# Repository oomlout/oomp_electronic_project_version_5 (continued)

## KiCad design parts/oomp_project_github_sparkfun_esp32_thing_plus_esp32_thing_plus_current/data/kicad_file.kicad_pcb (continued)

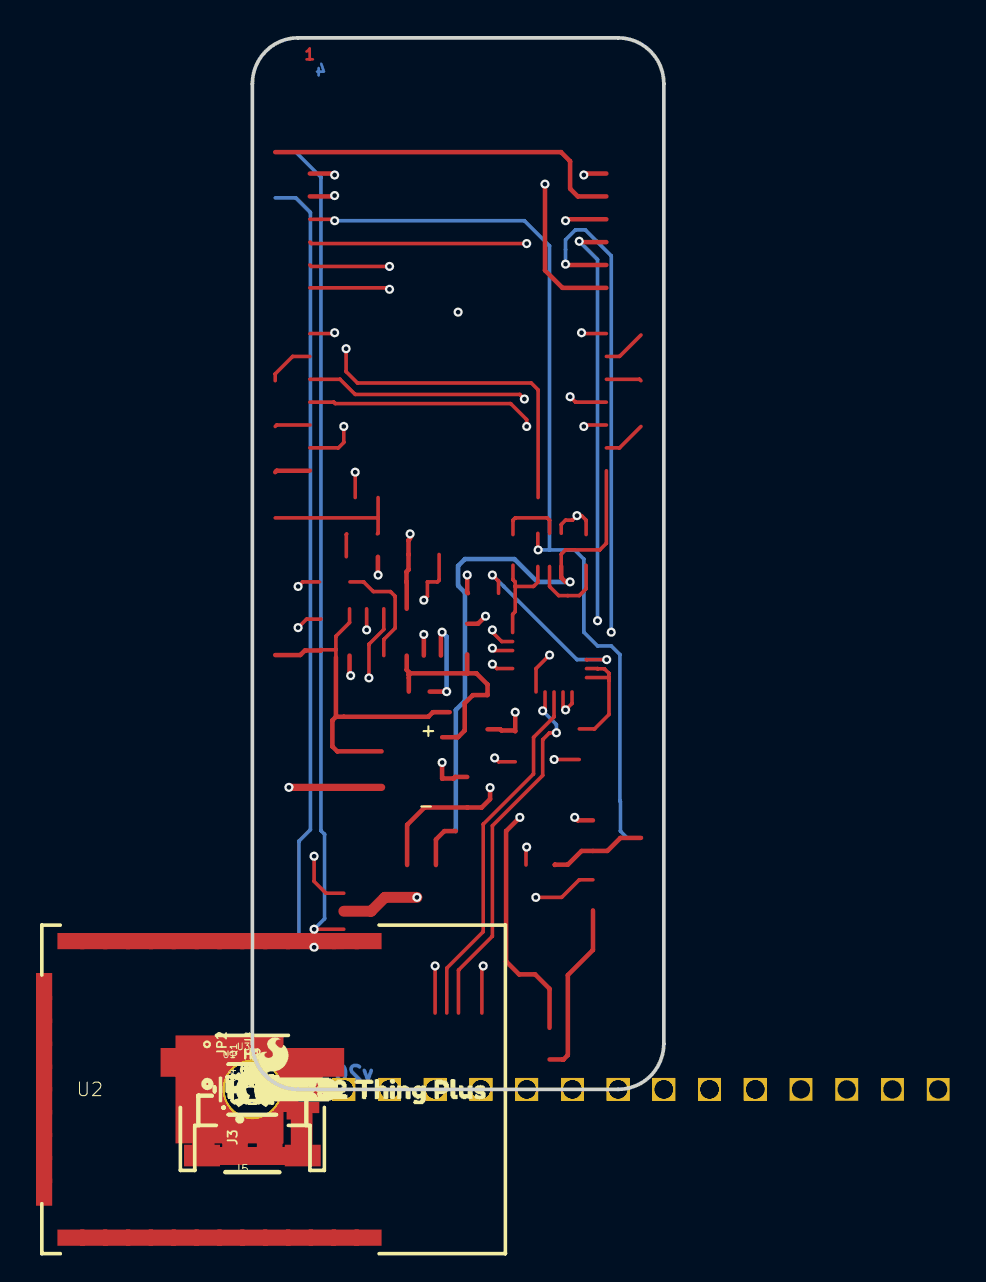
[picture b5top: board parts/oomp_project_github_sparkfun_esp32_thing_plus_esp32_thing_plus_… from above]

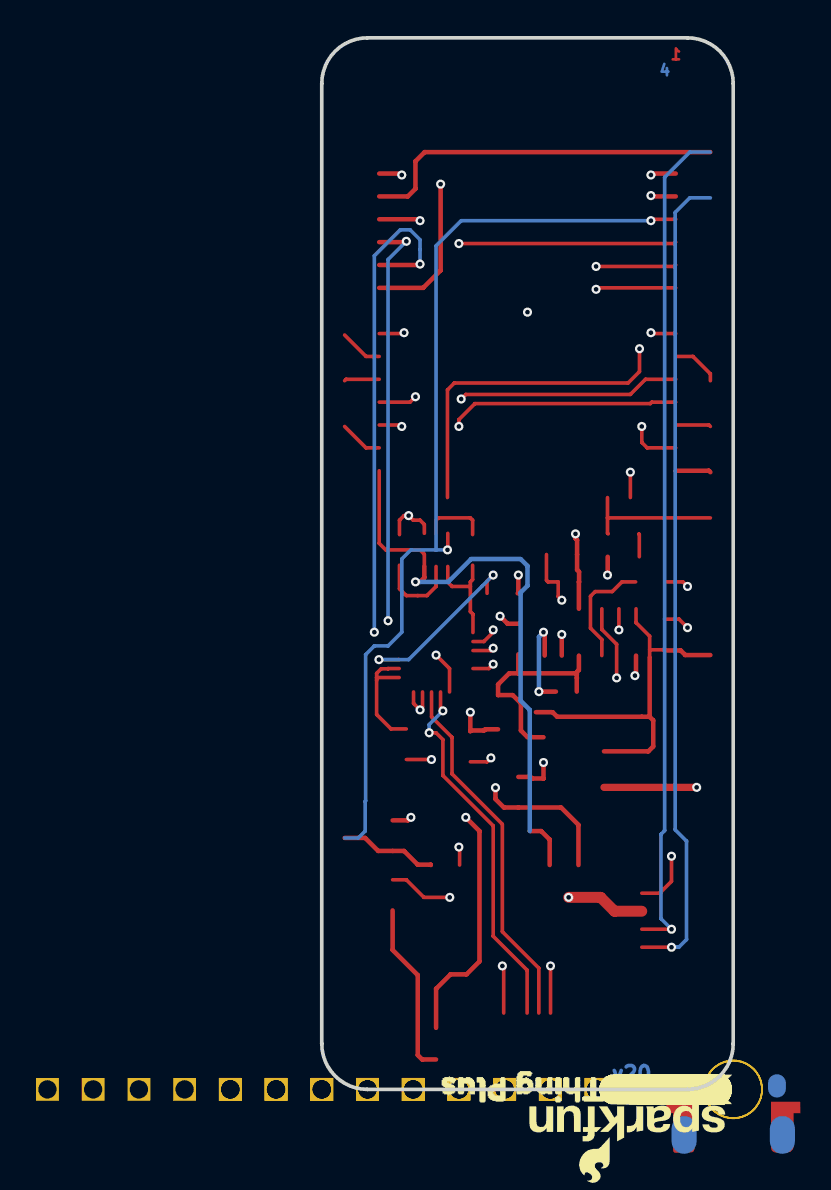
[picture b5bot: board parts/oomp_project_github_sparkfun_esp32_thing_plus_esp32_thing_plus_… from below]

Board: 4 copper layers, 22.9 x 58.4 mm, 107 parts (32 on the bottom side), 43 nets.

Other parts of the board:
U$1: #RESET0
U$2: 3V31
U$3: 1323
U$4: 1417
U$5: 1519
U$6: 16#RX11
U$7: 17#TX10
U$8: 121
U$9: 210
U$10: 2721
U$11: 3218
U$12: 3320
U$13: A03
U$14: A14
U$15: A25
U$16: A36
U$17: A47
U$18: A58
U$19: EN26
U$20: GND2
U$21: 22#SCL1
U$22: 23#SDA0
U$23: QWIIC27
U$27: VBAT25
U$28: VUSB24
U$29: SDA1
U$30: SCL0
U$31: 142
U$32: 323
U$33: 154
U$34: 335
U$35: 276
U$36: 127
U$37: 138
U$38: 219
U$39: 1710
U$40: 1611
U$41: A515
U$42: A416
U$43: A317
U$44: A218
U$45: A119
U$46: A020
U$47: SCK20
U$48: GND21
U$49: NC22
U$50: VUSB8
U$51: EN9
U$52: VBAT10
U$53: 137
U$54: MISO0
U$55: MOSI1
U$56: CHG1
U$57: RESET0
U$58, U$65: ESP32_THING_PLUS0
U$59: ORDERING_INSTRUCTIONS
U$60: 3V323
U$61: RST24
U$62: 00
U$63: 5#SCK2
U$64: NC0
U$66: 18#MOSI1
U$67: 19#MISO0

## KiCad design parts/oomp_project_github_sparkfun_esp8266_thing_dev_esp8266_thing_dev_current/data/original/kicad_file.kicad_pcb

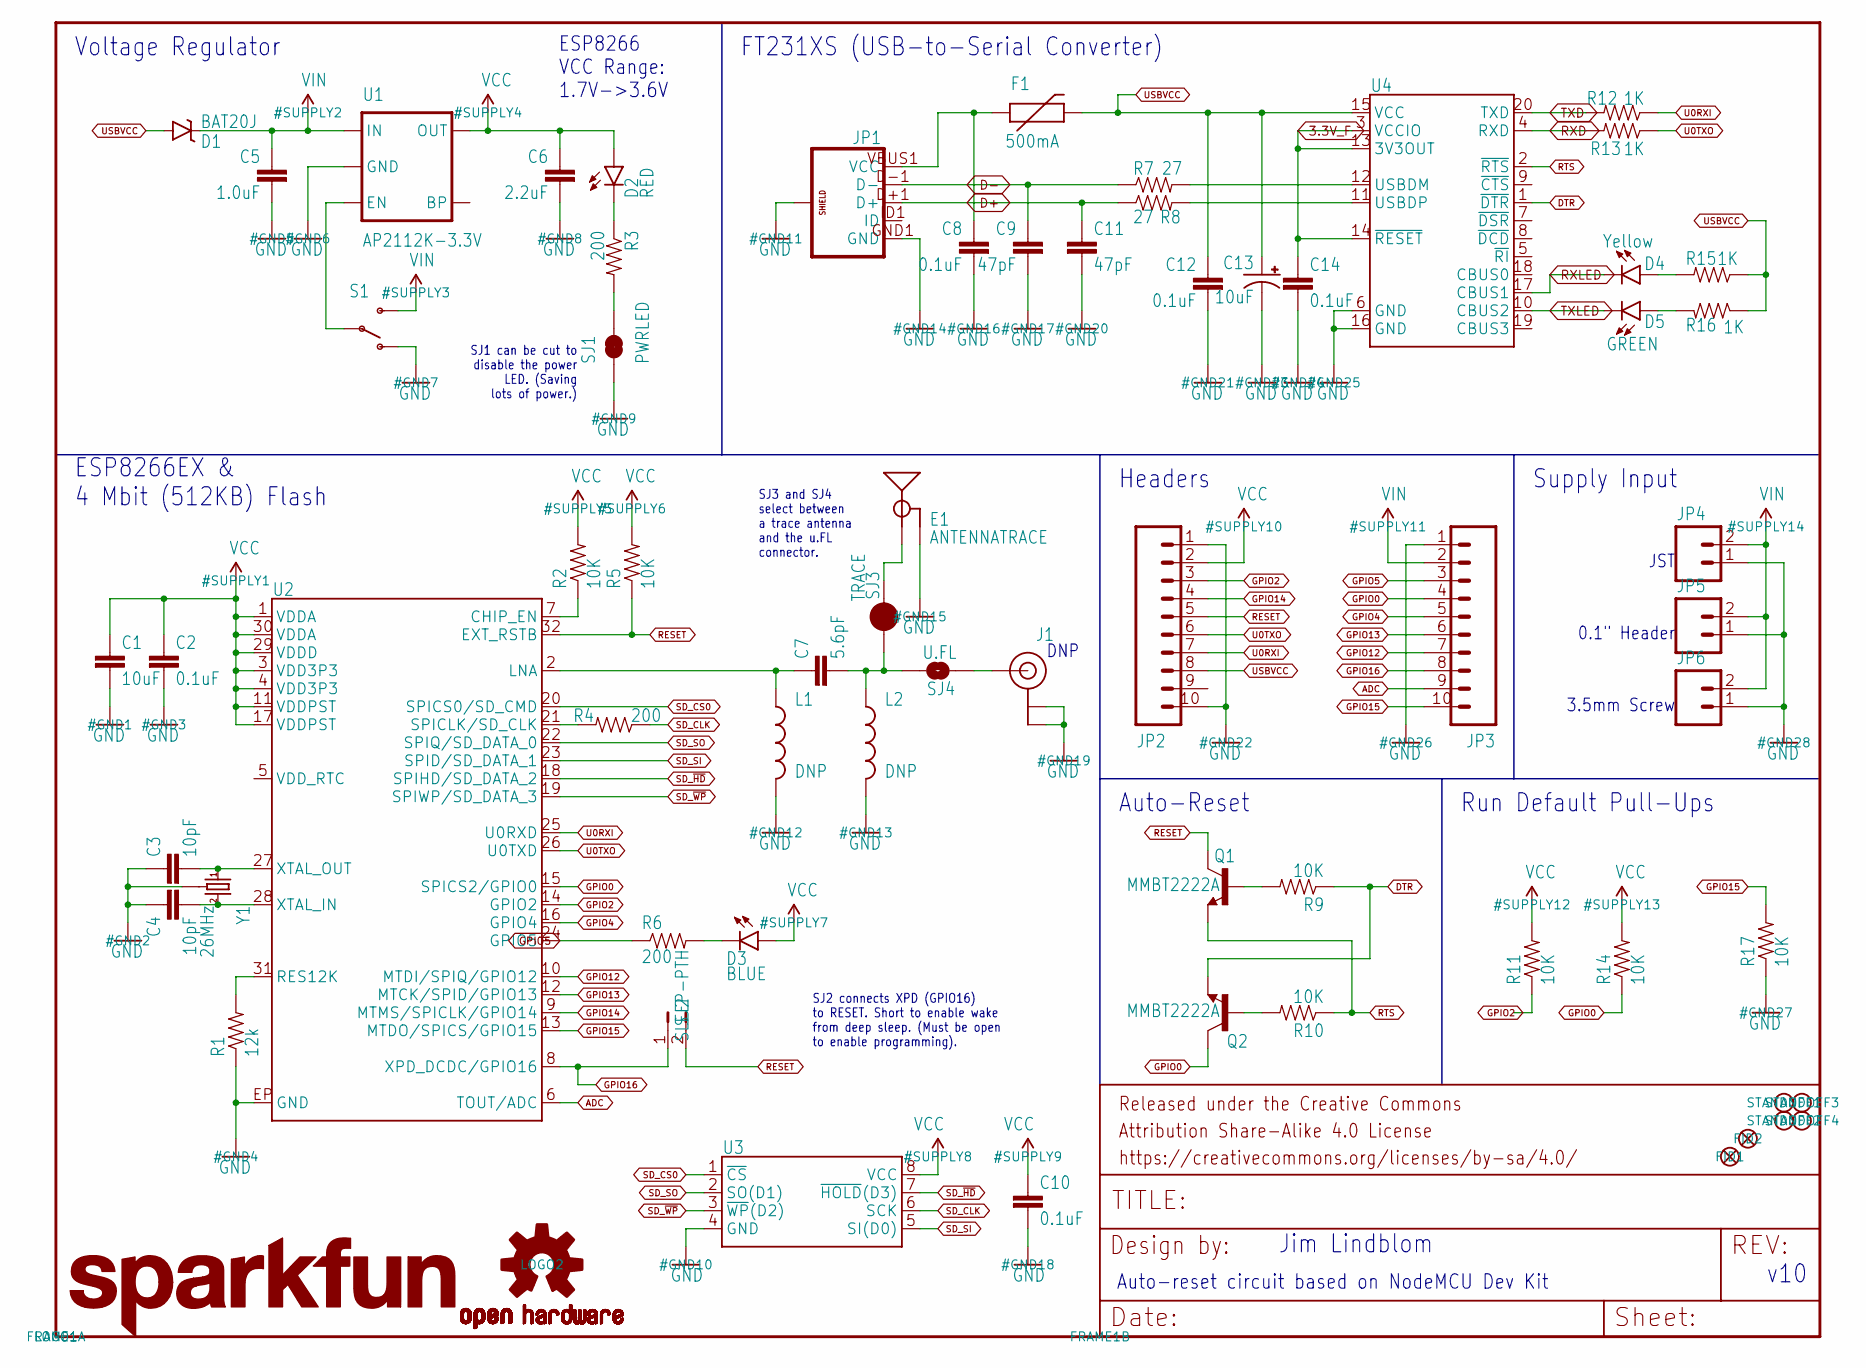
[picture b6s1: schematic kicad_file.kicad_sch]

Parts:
C1: 10uF; 0603-CAP
C2, C8, C10, C12, C14: 0.1uF; 0603-CAP
C3, C4: 10pF; 0603-CAP
C5: 1.0uF; 0805
C6: 2.2uF; 0603-CAP
C7: 5.6pF; 0603-CAP
C9, C11: 47pF; 0603-CAP
C13: 10uF; EIA3216
D1: BAT20J; SOD-323
D2: RED; LED-0603
D3: BLUE; LED-0603
D4: Yellow; LED-0603
D5: GREEN; LED-0603
E1: ANTENNATRACE; TRACE_ANTENNA_2.4GHZ_25.7MM
F1: 500mA; PTC-1206
FID1, FID2: FIDUCIAL1X2; FIDUCIAL-1X2
FRAME1: FRAME-LETTER; CREATIVE_COMMONS
J1: DNP; U.FL
JP1: USB_MICROB_PLUGCONN-11752; USB-B-MICRO-SMD_V03
JP2, JP3: M10NO_SILK_PTH_FEMALE; 1X10_NO_SILK
JP4: M02JST-PTH-2; JST-2-PTH
JP5: M021X02_NO_SILK; 1X02_NO_SILK
JP6: M023.5MM-NO_SILK; SCREWTERMINAL-3.5MM-2-NS
L1, L2: DNP; 0603
LOGO1: SFE_LOGO_NAME.2_INCH; SFE_LOGO_NAME_.2
LOGO2: OSHW-LOGOS; OSHW-LOGO-S
Q1, Q2: MMBT2222A; SOT23-3
R1: 12k; 0603-RES
R2, R5, R9, R10, R11, R14, R17: 10K; 0603-RES
R3, R4, R6: 200; 0603-RES
R7, R8: 27; 0603-RES
R12, R13, R15, R16: 1K; 0603-RES
S1: SWITCH-SPDT-SMD-A; SWITCH-SPST-SMD-A
SJ1: PWRLED; PAD-JUMPER-2-NC_BY_TRACE_YES_SILK
SJ2: SLEEP-PTH; PTH-JUMPER-2-NO_NO_SILK
SJ3: TRACE; PAD-JUMPER-2-NC_BY_PASTE_NO_SILK
SJ4: U.FL; PAD-JUMPER-2-NO_NO_SILK
STANDOFF1, STANDOFF2, STANDOFF3, STANDOFF4: STAND-OFF
U1: AP2112K-3.3V; SOT23-5
U2: ESP8266; QFN32
U3: AT25SF041-SOIC8; SO08
U4: FTS31XS-U; SSOP20_L
Y1: 26MHz; CRYSTAL-SMD-3.2X2.5

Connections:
3.3V_F: C14.1, U4.3 (VCCIO), U4.13 (3V3OUT), U4.14 (~RESET)
ADC: JP3.9, U2.6 (TOUT/ADC)
ANT: J1.P$3 (SIGNAL), SJ4.1
CHIP_EN: R2.1, U2.7 (CHIP_EN)
D+: C11.1, JP1.D+1 (D+), R8.1
D-: C9.1, JP1.D-1 (D-), R7.1
DTR: Q2.2 (E), R9.1, U4.1 (~DTR)
GND: C1.2, C2.2, C3.1, C4.1, C5.2, C6.2, C8.2, C9.2, C10.2, C11.2, C12.2, C13.C (-), C14.2, E1.GND, E1.GND2 (GND), J1.P$1 (GND), J1.P$2 (GND), JP1.GND1 (GND), JP1.SHIELD1 (SHIELD), JP1.SHIELD2 (SHIELD), JP1.SHIELD3 (SHIELD), JP2.1, JP2.10, JP3.1, JP4.1, JP5.1, JP6.1, L1.2, L2.2, R1.1, R17.1, S1.1 (O), SJ1.1, U1.2 (GND), U2.EP (GND), U3.4 (GND), U4.6 (GND), U4.16 (GND), Y1.2 (GND), Y1.4 (GND)
GPIO0: JP3.4, Q2.3 (C), R14.1, U2.15 (SPICS2/GPIO0)
GPIO2: JP2.3, R11.1, U2.14 (GPIO2)
GPIO4: JP3.5, U2.16 (GPIO4)
GPIO5: JP3.3, R6.1, U2.24 (GPIO5)
GPIO12: JP3.7, U2.10 (MTDI/SPIQ/GPIO12)
GPIO13: JP3.6, U2.12 (MTCK/SPID/GPIO13)
GPIO14: JP2.4, U2.9 (MTMS/SPICLK/GPIO14)
GPIO15: JP3.10, R17.2, U2.13 (MTDO/SPICS/GPIO15)
GPIO16: JP3.8, SJ2.1, U2.8 (XPD_DCDC/GPIO16)
LNA: C7.1, L1.1, U2.2 (LNA)
LNA2: C7.2, L2.1, SJ3.1, SJ4.2
unnamed: R1.2, U2.31 (RES12K)
unnamed: C4.2, U2.28 (XTAL_IN), Y1.3 (2)
unnamed: C3.2, U2.27 (XTAL_OUT), Y1.1
unnamed: R7.2, U4.12 (USBDM)
unnamed: R3.2, SJ1.2
unnamed: Q1.1 (B), R9.2
unnamed: R8.2, U4.11 (USBDP)
unnamed: D5.A, R16.2
unnamed: D3.C, R6.2
unnamed: D4.A, R15.2
unnamed: D2.C, R3.1
unnamed: Q2.1 (B), R10.2
unnamed: S1.2, U1.3 (EN)
RESET: JP2.5, Q1.3 (C), R5.1, SJ2.2, U2.32 (EXT_RSTB)
RTS: Q1.2 (E), R10.1, U4.2 (~RTS)
RXD: R13.2, U4.4 (RXD)
RXLED: D4.C, U4.17 (CBUS1)
SD_CLK: R4.1, U3.6 (SCK)
SD_CLK0: R4.2, U2.21 (SPICLK/SD_CLK)
SD_CS0: U2.20 (SPICS0/SD_CMD), U3.1 (~CS)
SD_SI: U2.23 (SPID/SD_DATA_1), U3.5 (SI(D0))
SD_SO: U2.22 (SPIQ/SD_DATA_0), U3.2 (SO(D1))
SD_~HD: U2.18 (SPIHD/SD_DATA_2), U3.7 (~HOLD(D3))
SD_~WP: U2.19 (SPIWP/SD_DATA_3), U3.3 (~WP(D2))
TRACE_ANT: E1.ANT (SIGNAL), SJ3.2
TXD: R12.2, U4.20 (TXD)
TXLED: D5.C, U4.10 (CBUS2)
U0RXI: JP2.7, R12.1, U2.25 (U0RXD)
U0TXO: JP2.6, R13.1, U2.26 (U0TXD)
USBVCC: C12.1, C13.A (+), D1.A, F1.2, JP2.8, R15.1, R16.1, U4.15 (VCC)
VCC: C1.1, C2.1, C6.1, C10.1, D2.A, D3.A, JP2.2, R2.2, R5.2, R11.2, R14.2, U1.5 (OUT), U2.1 (VDDA), U2.3 (VDD3P3), U2.4 (VDD3P3), U2.11 (VDDPST), U2.17 (VDDPST), U2.29 (VDDD), U2.30 (VDDA), U3.8 (VCC)
VIN: C5.1, D1.C, JP3.2, JP4.2, JP5.2, JP6.2, S1.3 (S), U1.1 (IN)
VUSB: C8.1, F1.1, JP1.VBUS1 (VCC)

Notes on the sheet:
DNP
Jim Lindblom
Supply Input
ESP8266 VCC Range: 1.7V->3.6V
3.5mm Screw
Auto-reset circuit based on NodeMCU Dev Kit
0.1" Header
Auto-Reset
ESP8266EX & 4 Mbit (512KB) Flash
SJ2 connects XPD (GPIO16) to RESET. Short to enable wake from deep sleep. (Must be open to enable programming).
JST
Voltage Regulator
SJ1 can be cut to disable the power LED. (Saving lots of power.)
SJ3 and SJ4 select between a trace antenna and the u.FL connector.
Headers
Run Default Pull-Ups
v10
FT231XS (USB-to-Serial Converter)

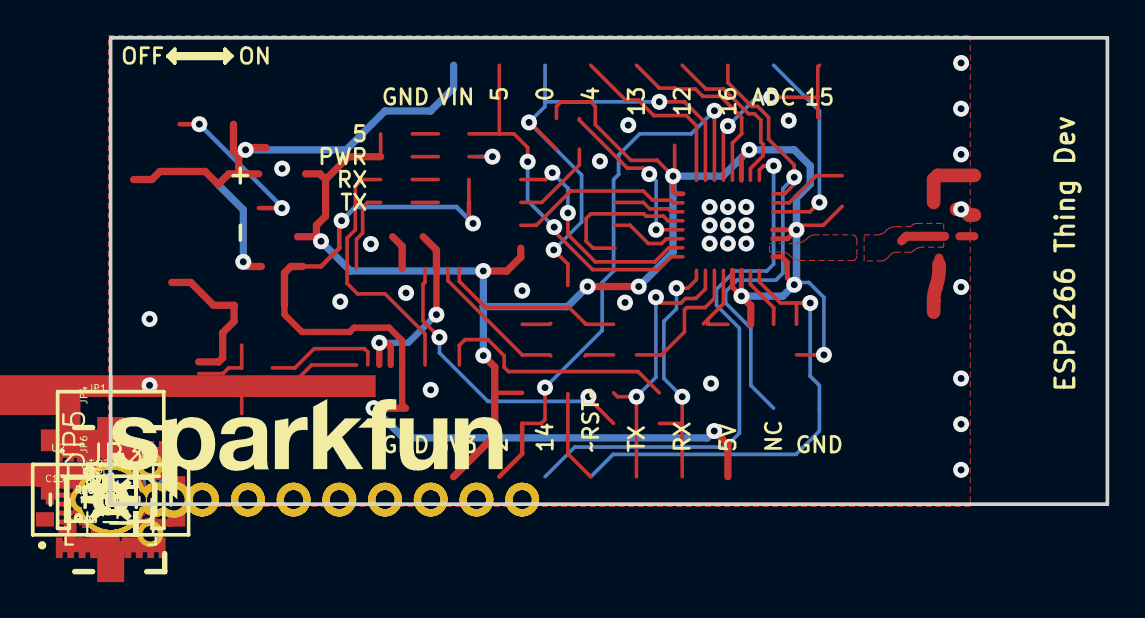
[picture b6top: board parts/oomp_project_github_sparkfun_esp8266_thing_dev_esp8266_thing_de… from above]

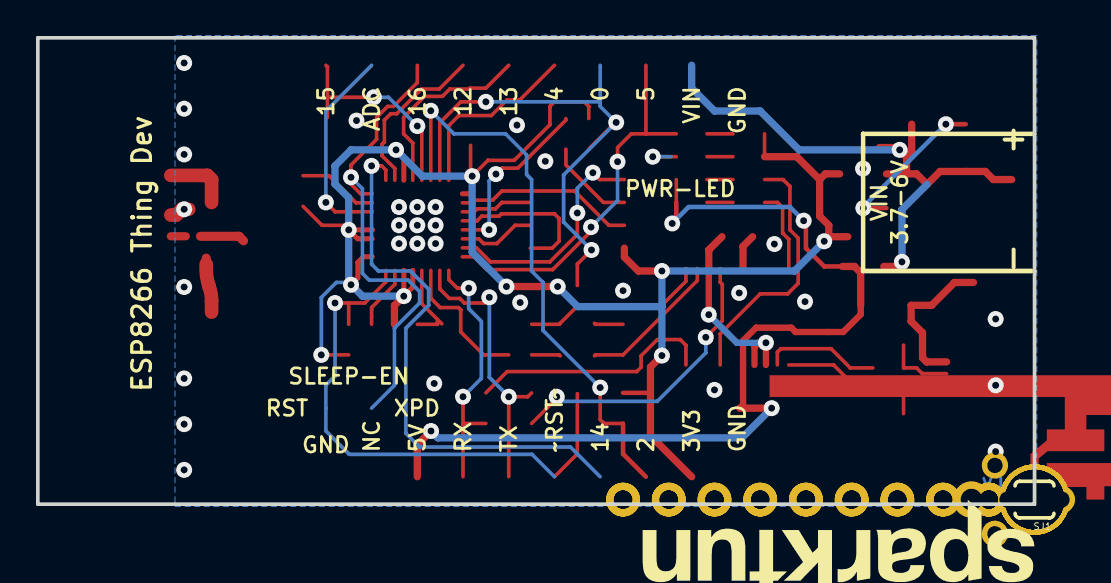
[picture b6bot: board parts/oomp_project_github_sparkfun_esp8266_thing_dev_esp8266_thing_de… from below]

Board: 2 copper layers, 55.4 x 25.9 mm, 69 parts (2 on the bottom side), 52 nets.

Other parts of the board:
LOGO3: SFE_LOGO_NAME.2_INCH; SFE_LOGO_NAME_.2

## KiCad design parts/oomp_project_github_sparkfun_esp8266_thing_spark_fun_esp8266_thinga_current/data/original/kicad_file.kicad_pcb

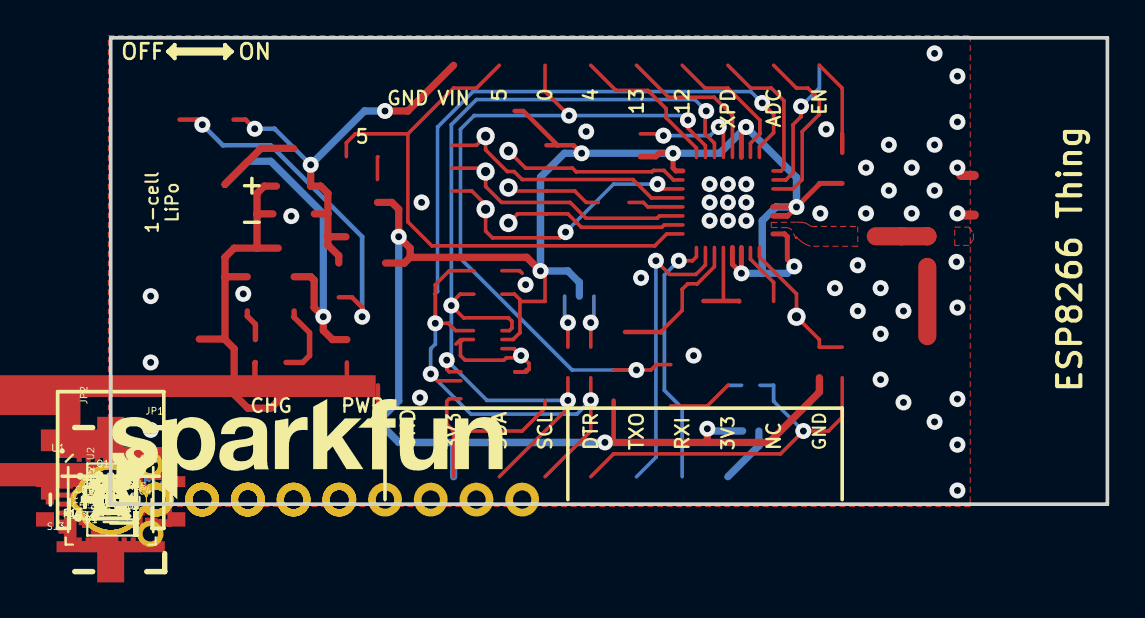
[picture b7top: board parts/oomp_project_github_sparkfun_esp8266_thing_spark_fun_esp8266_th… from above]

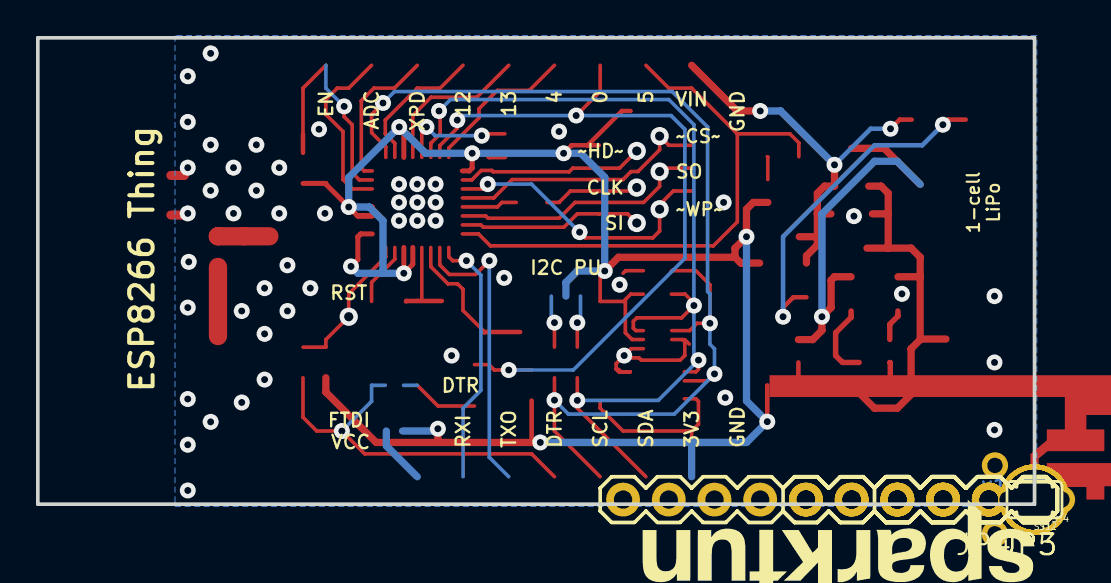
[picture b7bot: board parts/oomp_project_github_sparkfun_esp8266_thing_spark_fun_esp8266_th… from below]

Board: 2 copper layers, 55.4 x 25.9 mm, 73 parts (14 on the bottom side), 44 nets.

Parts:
C1: 10uF; 0603-CAP
C2, C10: 0.1uF; 0603-CAP
C3, C4: 10pF; 0603-CAP
C5: 4.7uF; 0603-CAP
C6: 1.0uF; 0603-CAP
C7: 1.0uF; 0805
C8: 5.6pF; 0603-CAP
C9: 2.2uF; 0603-CAP
C11, C12: DNP; 0603-CAP
D1: YELLOW; LED-0603
D2: GREEN; LED-0603
D3: BAT20J; SOD-323
D4: RED; LED-0603
D5: SOD-323
E1: ANTENNATRACE; TRACE_ANTENNA_2.4GHZ_25.7MM
FID1, FID2: FIDUCIAL1X2; FIDUCIAL-1X2
FRAME1: FRAME-LETTER; CREATIVE_COMMONS
J1: DNP; U.FL
JP1: USB; USB-B-MICRO-SMD_V03
JP2: LiPo; JST-2-PTH
JP3: M10"; 1X10
JP4: FTDI_BASICPTH; FTDI_BASIC
JP5: I2C; 1X04
L1, L2: DNP; 0603
LOGO1, LOGO5: SFE_LOGO_NAME.2_INCH; SFE_LOGO_NAME_.2
LOGO3: SFE_LOGO_FLAME.1_INCH; SFE_LOGO_FLAME_.1
LOGO4: OSHW-LOGOS; OSHW-LOGO-S
Q1: 2.5A/30V; SOT23-3
R1: 12k; 0603-RES
R2, R5, R8, R16: 200; 0603-RES
R3, R6, R7, R17: 10K; 0603-RES
R4: 2.0k; 0603-RES
R9: 0; 0603
R10: DNP; 0603-RES
R11, R13: 2.2k; 0603-RES
R15: 1K; 0603-RES
S1: SWITCH-SPST-SMD-A
SJ1: PAD-JUMPER-2-NC_BY_TRACE_YES_SILK
SJ2: PAD-JUMPER-3-3OF3_NC_BY_TRACE_YES_SILK_FULL_BOX
SJ3: PTH-JUMPER-NC_BOTTOM_NO_SILK
SJ4: PAD-JUMPER-2-NO_YES_SILK
STANDOFF1, STANDOFF2, STANDOFF3, STANDOFF4: STAND-OFF
TP1, TP2, TP3, TP4, TP5, TP6, TP7: PAD.03X.05
U1: ESP8266; QFN32
U2: MCP73831; SOT23-5
U3: AT25SF041-SOIC8; SO08
U4: AP2112K-3.3V; SOT23-5
U5: DNP; UDFN8
U6: DNP; SOT563-2
U7: DNP; FN-6
Y1: 26MHz; CRYSTAL-SMD-3.2X2.5

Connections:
ADC: JP3.9, U1.6
ANT: J1.P$3, R10.1
CHIP_EN: JP3.10, R3.1, U1.7
DTR: C6.2, JP4.DTR, SJ1.2, SJ3.1
FTDI_VCC: JP4.VCC, SJ4.1
GND: C1.2, C2.2, C3.1, C4.1, C5.2, C7.2, C9.2, C10.2, C11.2, C12.2, E1.GND, E1.GND2, J1.P$1, J1.P$2, JP1.GND1, JP1.SHIELD1, JP1.SHIELD2, JP1.SHIELD3, JP2.1, JP3.1, JP4.GND, JP5.1, L1.2, L2.2, R1.1, R4.1, R7.1, R8.2, R16.2, R17.1, S1.1, U1.EP, U2.2, U3.4, U4.2, U5.4, U6.2, U6.4, U7.2, U7.3, Y1.2, Y1.4
GPIO0: D5.A, JP3.4, R15.1, U1.15
GPIO2/SDA: JP5.3, R11.1, U1.14, U5.5, U6.6, U7.6
GPIO4: JP3.5, U1.16
GPIO5: D2.A, JP3.3, U1.24
GPIO12: JP3.7, U1.10
GPIO13: JP3.6, U1.12
GPIO14/SCL: JP5.4, R13.1, U1.9, U5.6, U6.1, U7.4
GPIO15: R17.2, U1.13
GPIO16: JP3.8, U1.8
LNA: C8.1, L1.1, U1.2
unnamed: R1.2, U1.31
unnamed: C4.2, U1.28, Y1.3
unnamed: C3.2, U1.27, Y1.1
unnamed: D4.C, R16.1
unnamed: C8.2, L2.1, R9.2, R10.2
unnamed: R5.2, U1.21
unnamed: D5.C, SJ1.1, SJ3.2
unnamed: R11.2, SJ2.1
unnamed: R13.2, SJ2.3
unnamed: S1.2, U4.3
unnamed: R4.2, U2.5
unnamed: D2.C, R8.1
unnamed: D1.C, R2.2
unnamed: R2.1, U2.1
RESET: C6.1, R6.1, TP7.P$1, U1.32
SD_CLK: R5.1, TP3.P$1, U3.6
SD_CS0: TP6.P$1, U1.20, U3.1
SD_SI: TP2.P$1, U1.23, U3.5
SD_SO: TP5.P$1, U1.22, U3.2
SD_~HD: TP4.P$1, U1.18, U3.7
SD_~WP: TP1.P$1, U1.19, U3.3
TRACE_ANT: E1.ANT, R9.1
U0RXI: JP4.TXO, U1.25
U0TXO: JP4.RXI, U1.26
VBAT: C5.1, JP2.2, Q1.3, U2.3
VCC: C1.1, C2.1, C9.1, C10.1, C11.1, C12.1, D4.A, JP5.2, R3.2, R6.2, R15.2, SJ2.2, SJ4.2, U1.1, U1.3, U1.4, U1.11, U1.17, U1.29, U1.30, U3.8, U4.5, U5.8, U6.5, U7.1
VIN: C7.1, D3.C, JP3.2, Q1.2, S1.3, U4.1
VUSB: D1.A, D3.A, JP1.VBUS1, Q1.1, R7.2, U2.4

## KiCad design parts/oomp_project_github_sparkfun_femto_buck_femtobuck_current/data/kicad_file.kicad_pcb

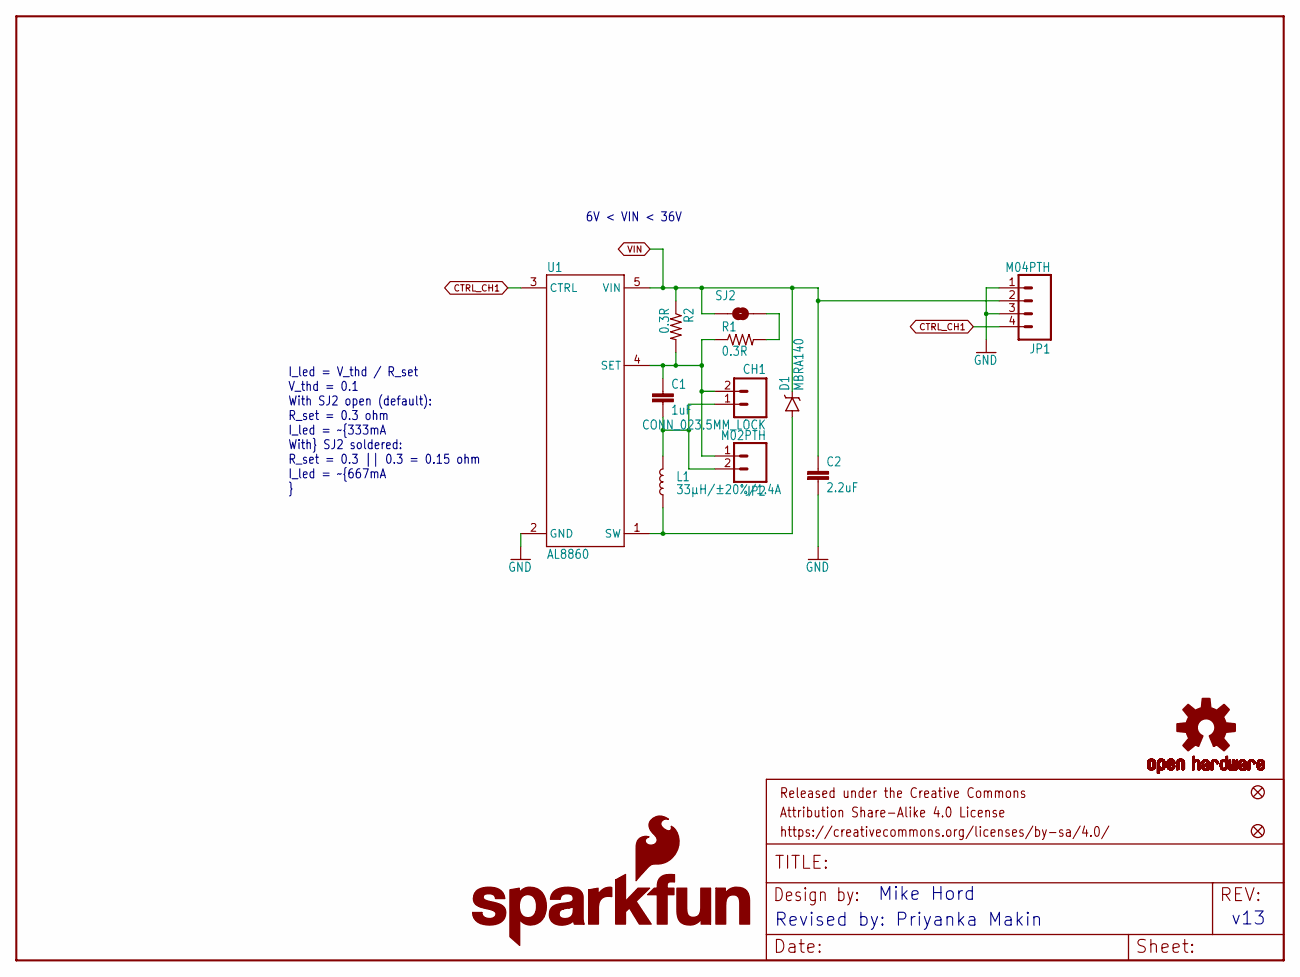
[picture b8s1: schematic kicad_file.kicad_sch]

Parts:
C1: 1uF; 1206-CAP
C2: 2.2uF; 1206-CAP
CH1: CONN_023.5MM_LOCK; SCREWTERMINAL-3.5MM-2_LOCK
D1: MBRA140; SMA-DIODE
FID1, FID2: FIDUCIAL1X2; FIDUCIAL-1X2
FRAME1: FRAME-LETTER; CREATIVE_COMMONS
JP1: M04PTH; 1X04
JP2: M02PTH; 1X02@1
L1: 33µH/±20%/1.4A; SRN6045
LOGO1: OSHW-LOGOS; OSHW-LOGO-S
LOGO2: SFE_LOGO_NAME_FLAME.1_INCH; SFE_LOGO_NAME_FLAME_.1
R1, R2: 0.3R; 0805
SJ2: NO Jumper; SMT-JUMPER_2_NO_NO-SILK
U1: AL8860; SOT23-5

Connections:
CTRL_CH1: JP1.4, U1.3 (CTRL)
GND: C2.2, JP1.1, JP1.3, U1.2 (GND)
unnamed: R1.2, SJ2.2
OUT+: C1.1, CH1.2, JP2.1, R1.1, R2.2, U1.4 (SET)
OUT-: C1.2, CH1.1, JP2.2, L1.2
SW: D1.A, L1.1, U1.1 (SW)
VIN: C2.1, D1.C, JP1.2, R2.1, SJ2.1, U1.5 (VIN)

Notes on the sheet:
6V < VIN < 36V
Mike Hord
Revised by: Priyanka Makin
v13
I_led = V_thd / R_set V_thd = 0.1 With SJ2 open (default): R_set = 0.3 ohm I_led = ~{333mA With} SJ2 soldered: R_set = 0.3 || 0.3 = 0.15 ohm I_led = ~{667mA }

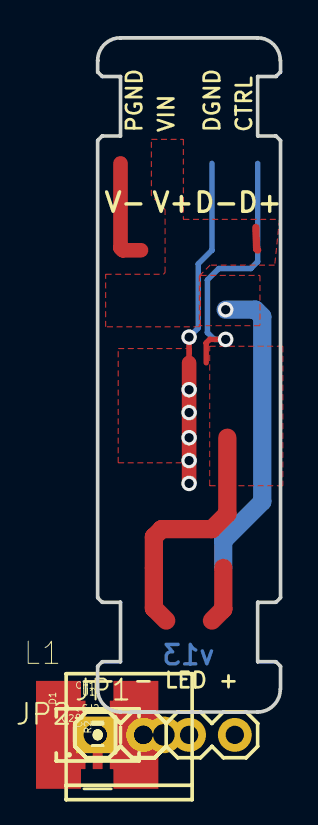
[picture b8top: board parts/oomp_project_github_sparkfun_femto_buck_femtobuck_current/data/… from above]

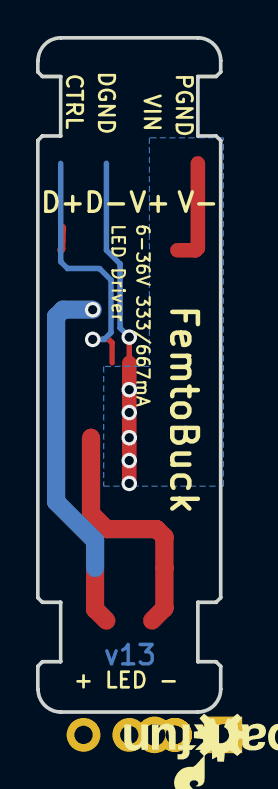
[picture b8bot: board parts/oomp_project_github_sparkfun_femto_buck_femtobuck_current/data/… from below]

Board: 4 copper layers, 10.2 x 37.5 mm, 16 parts (2 on the bottom side), 7 nets.

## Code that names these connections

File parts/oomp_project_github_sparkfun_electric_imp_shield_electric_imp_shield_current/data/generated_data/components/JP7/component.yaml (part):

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      position:
        x: 254.0
        y: 147.32
      net: PIN9
      net_aliases:
      - PIN9
      net_scope: global
      no_connect: false
      connected_to:
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      position:
        x: 254.0
        y: 144.78
      net: PIN8
      net_aliases:
      - PIN8
      net_scope: global
      no_connect: false
      connected_to:
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      position:
        x: 254.0
        y: 142.24
      net: PIN7
      net_aliases:
      - PIN7
      net_scope: global
      no_connect: false
      connected_to:
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      position:
        x: 254.0
        y: 139.7
      net: PIN5
      net_aliases:
      - PIN5
      net_scope: global
      no_connect: false
      connected_to:
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      position:
        x: 254.0
        y: 137.16
      net: PIN2
      net_aliases:
      - PIN2
      net_scope: global
      no_connect: false
      connected_to:
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      position:
        x: 254.0
        y: 134.62
      net: PIN1
      net_aliases:
      - PIN1
      net_scope: global
      no_connect: false
      connected_to:
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    layers:
    - '*.Cu'
    - '*.Mask'
    net: PIN9
    net_number: null
    pin_function: null
    pin_type: null
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    layers:
    - '*.Cu'
    - '*.Mask'
    net: PIN8
    net_number: null
    pin_function: null
    pin_type: null
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    layers:
    - '*.Cu'
    - '*.Mask'
    net: PIN7
    net_number: null
    pin_function: null
    pin_type: null
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    layers:
    - '*.Cu'
    - '*.Mask'
    net: PIN5
    net_number: null
    pin_function: null
    pin_type: null
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    layers:
    - '*.Cu'
    - '*.Mask'
    net: PIN2
    net_number: null
    pin_function: null
    pin_type: null
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    layers:
    - '*.Cu'
    - '*.Mask'
    net: PIN1
    net_number: null
    pin_function: null
    pin_type: null
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    status: agree
  - pin_or_pad_number: '4'
    schematic_nets:
    - PIN9
    pcb_nets:
    - PIN9
    status: agree
  - pin_or_pad_number: '5'
    schematic_nets:
    - PIN8
    pcb_nets:
    - PIN8
    status: agree
  - pin_or_pad_number: '6'
    schematic_nets:
    - PIN7
    pcb_nets:
    - PIN7
    status: agree
  - pin_or_pad_number: '7'
    schematic_nets:
    - PIN5
    pcb_nets:
    - PIN5
    status: agree
  - pin_or_pad_number: '8'
    schematic_nets:
    - PIN2
    pcb_nets:
    - PIN2
    status: agree
  - pin_or_pad_number: '9'
    schematic_nets:
    - PIN1
    pcb_nets:
    - PIN1
    status: agree
  agree_count: 9
  disagree_count: 0
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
